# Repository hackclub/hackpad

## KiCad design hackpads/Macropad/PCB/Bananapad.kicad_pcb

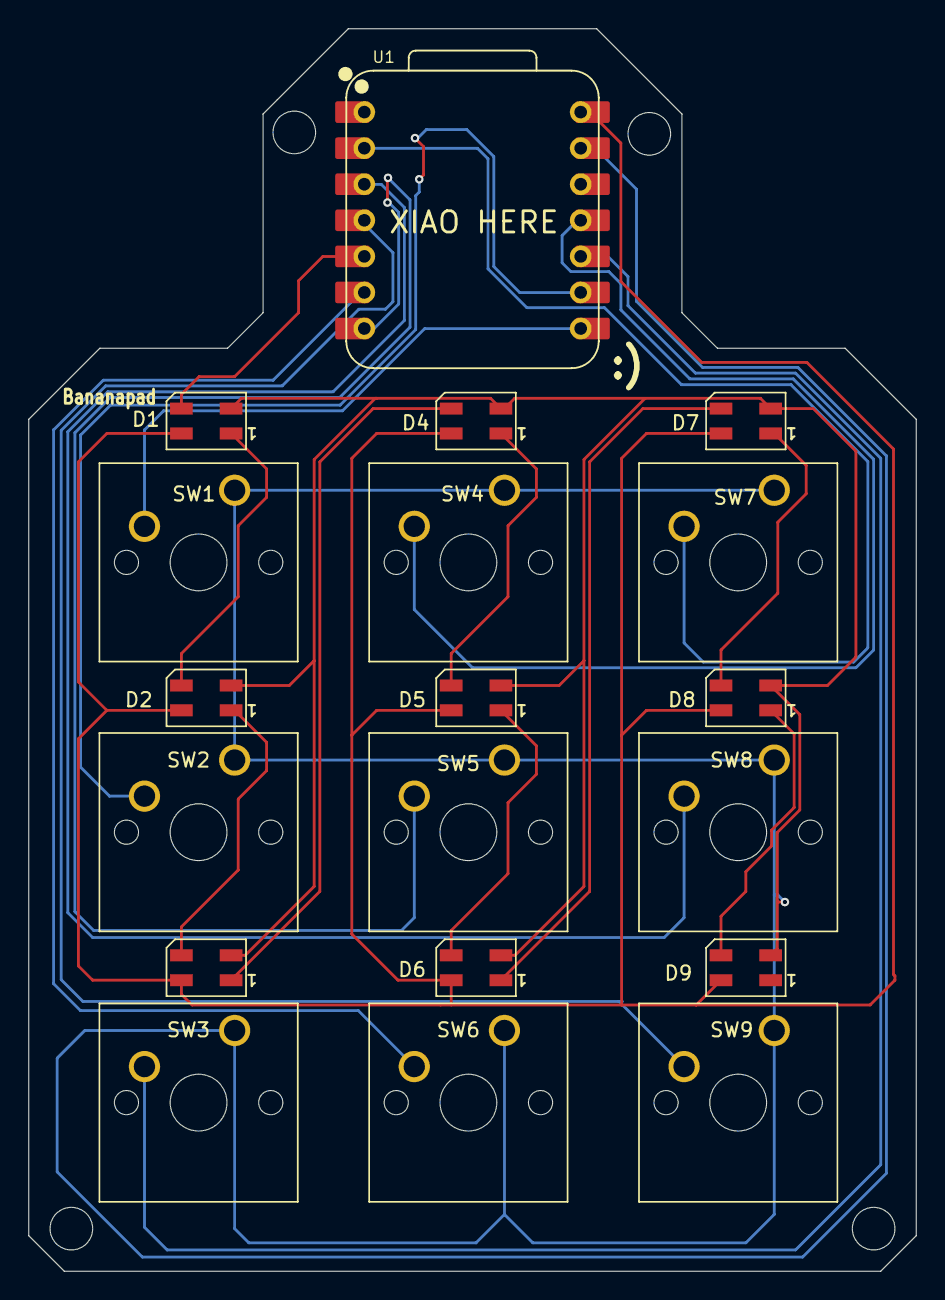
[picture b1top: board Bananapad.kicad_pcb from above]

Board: 2 copper layers, 62.5 x 87.5 mm, 19 parts (0 on the bottom side), 20 nets.

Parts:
D1, D2, D3, D4, D5, D6, D7, D8, D9: SK6812MINI; LED_SK6812MINI_PLCC4_3.5x3.5mm_P1.75mm
SW1, SW2, SW3, SW4, SW5, SW6, SW7, SW8, SW9: SW_Push; SW_Cherry_MX_1.00u_PCB
U1: XIAO-RP2040-DIP

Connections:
+5V: D1.4 (VDD), D2.4 (VDD), D3.4 (VDD), D4.4 (VDD), D5.4 (VDD), D6.4 (VDD), D7.4 (VDD), D8.4 (VDD), D9.4 (VDD), U1.14 (VBUS)
GND: D1.2 (VSS), D2.2 (VSS), D3.2 (VSS), D4.2 (VSS), D5.2 (VSS), D6.2 (VSS), D7.2 (VSS), D8.2 (VSS), D9.2 (VSS), SW1.1, SW2.1, SW3.1, SW4.1, SW5.1, SW6.1, SW7.1, SW8.1, SW9.1, U1.13 (GND)
unnamed: D1.3 (DIN), U1.5 (GPIO6/SDA)
unnamed: D1.1 (DOUT), D2.3 (DIN)
unnamed: D2.1 (DOUT), D3.3 (DIN)
unnamed: D3.1 (DOUT), D4.3 (DIN)
unnamed: D4.1 (DOUT), D5.3 (DIN)
unnamed: D5.1 (DOUT), D6.3 (DIN)
unnamed: D6.1 (DOUT), D7.3 (DIN)
unnamed: D7.1 (DOUT), D8.3 (DIN)
unnamed: D8.1 (DOUT), D9.3 (DIN)
unnamed: SW5.2, U1.7 (GPIO0/TX)
unnamed: SW1.2, U1.8 (GPIO1/RX)
unnamed: SW2.2, U1.9 (GPIO2/SCK)
unnamed: SW4.2, U1.11 (GPIO3/MOSI)
unnamed: SW3.2, U1.10 (GPIO4/MISO)
unnamed: SW6.2, U1.6 (GPIO7/SCL)
unnamed: SW7.2, U1.2 (GPIO27/ADC1/A1)
unnamed: SW8.2, U1.3 (GPIO28/ADC2/A2)
unnamed: SW9.2, U1.4 (GPIO29/ADC3/A3)

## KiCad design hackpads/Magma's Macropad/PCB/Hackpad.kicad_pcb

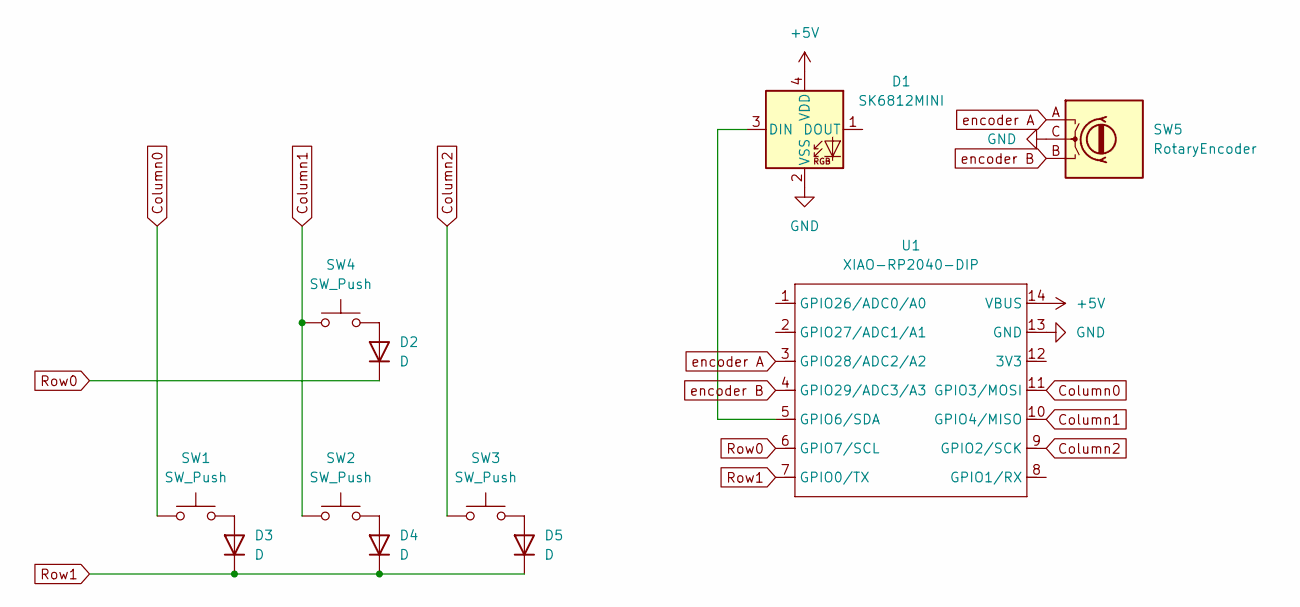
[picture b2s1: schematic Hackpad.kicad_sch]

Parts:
D1: SK6812MINI; LED_SK6812MINI_PLCC4_3.5x3.5mm_P1.75mm
D2, D3, D4, D5: D; D_DO-35_SOD27_P7.62mm_Horizontal
SW1, SW2, SW3, SW4: SW_Push; SW_Cherry_MX_1.00u_PCB
SW5: RotaryEncoder; RotaryEncoder_Alps_EC11E_Vertical_H20mm
U1: XIAO-RP2040-DIP

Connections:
+5V: D1.4 (VDD), U1.14 (VBUS)
Column0: SW1.1, U1.11 (GPIO3/MOSI)
Column1: SW2.1, SW4.1, U1.10 (GPIO4/MISO)
Column2: SW3.1, U1.9 (GPIO2/SCK)
GND: D1.2 (VSS), SW5.C, U1.13 (GND)
unnamed: D1.3 (DIN), U1.5 (GPIO6/SDA)
unnamed: D2.2 (A), SW4.2
unnamed: D3.2 (A), SW1.2
unnamed: D4.2 (A), SW2.2
unnamed: D5.2 (A), SW3.2
Row0: D2.1 (K), U1.6 (GPIO7/SCL)
Row1: D3.1 (K), D4.1 (K), D5.1 (K), U1.7 (GPIO0/TX)
encoder A: SW5.A, U1.3 (GPIO28/ADC2/A2)
encoder B: SW5.B, U1.4 (GPIO29/ADC3/A3)

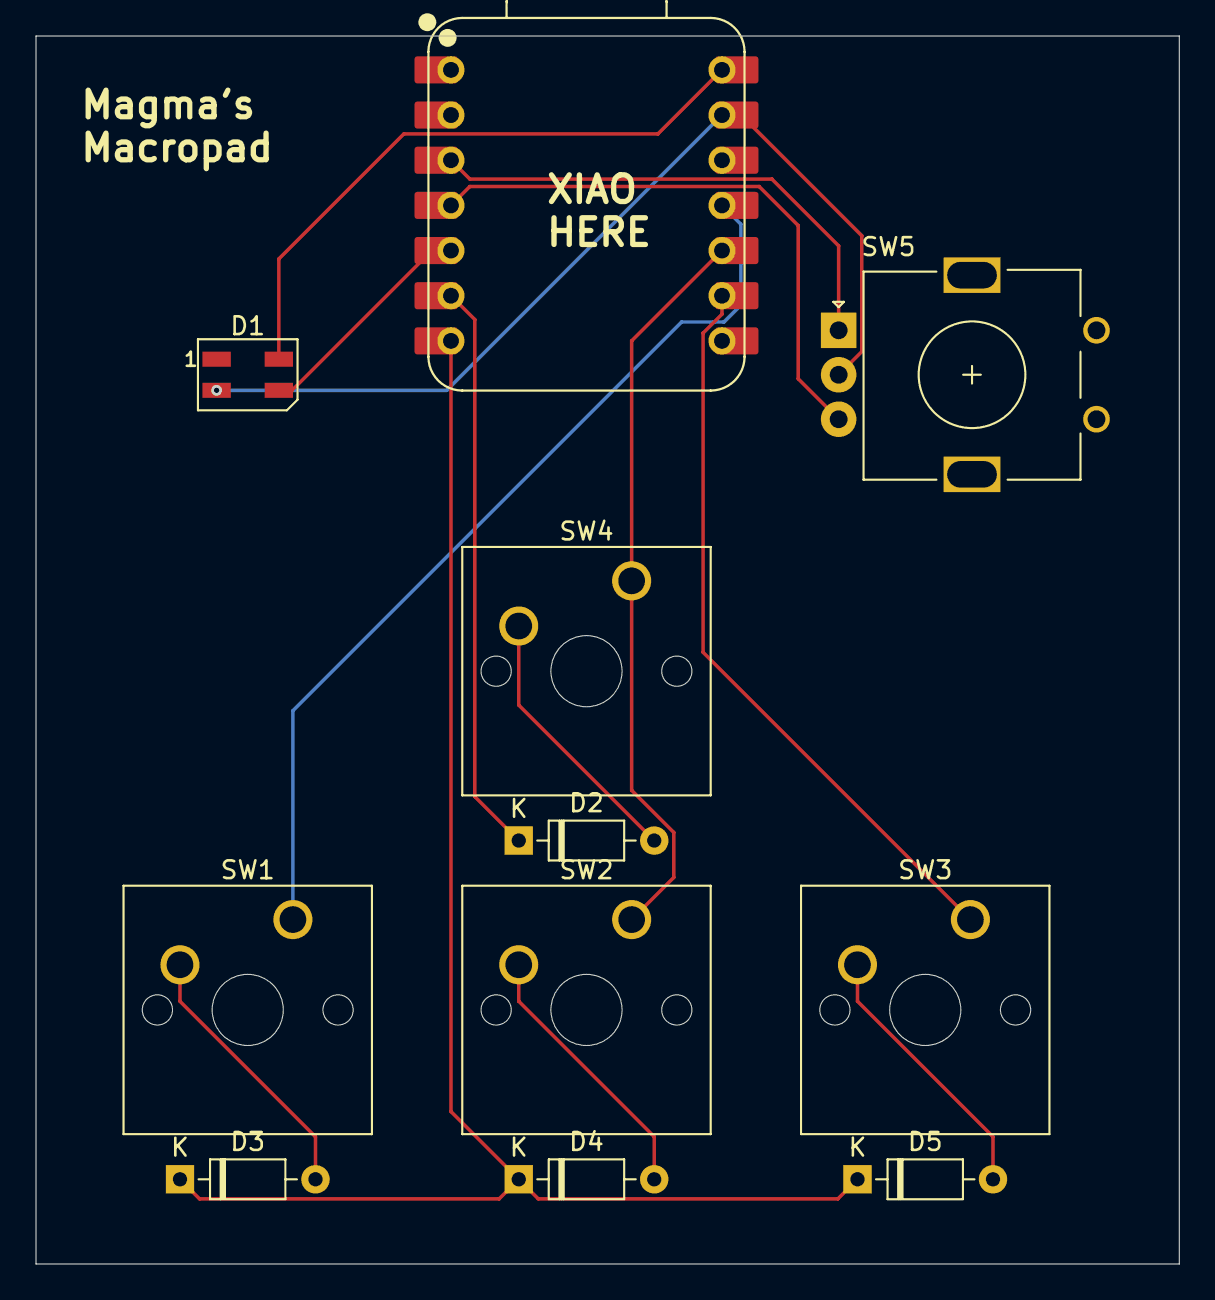
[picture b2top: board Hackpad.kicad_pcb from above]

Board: 2 copper layers, 64.3 x 69.1 mm, 11 parts (0 on the bottom side), 14 nets.

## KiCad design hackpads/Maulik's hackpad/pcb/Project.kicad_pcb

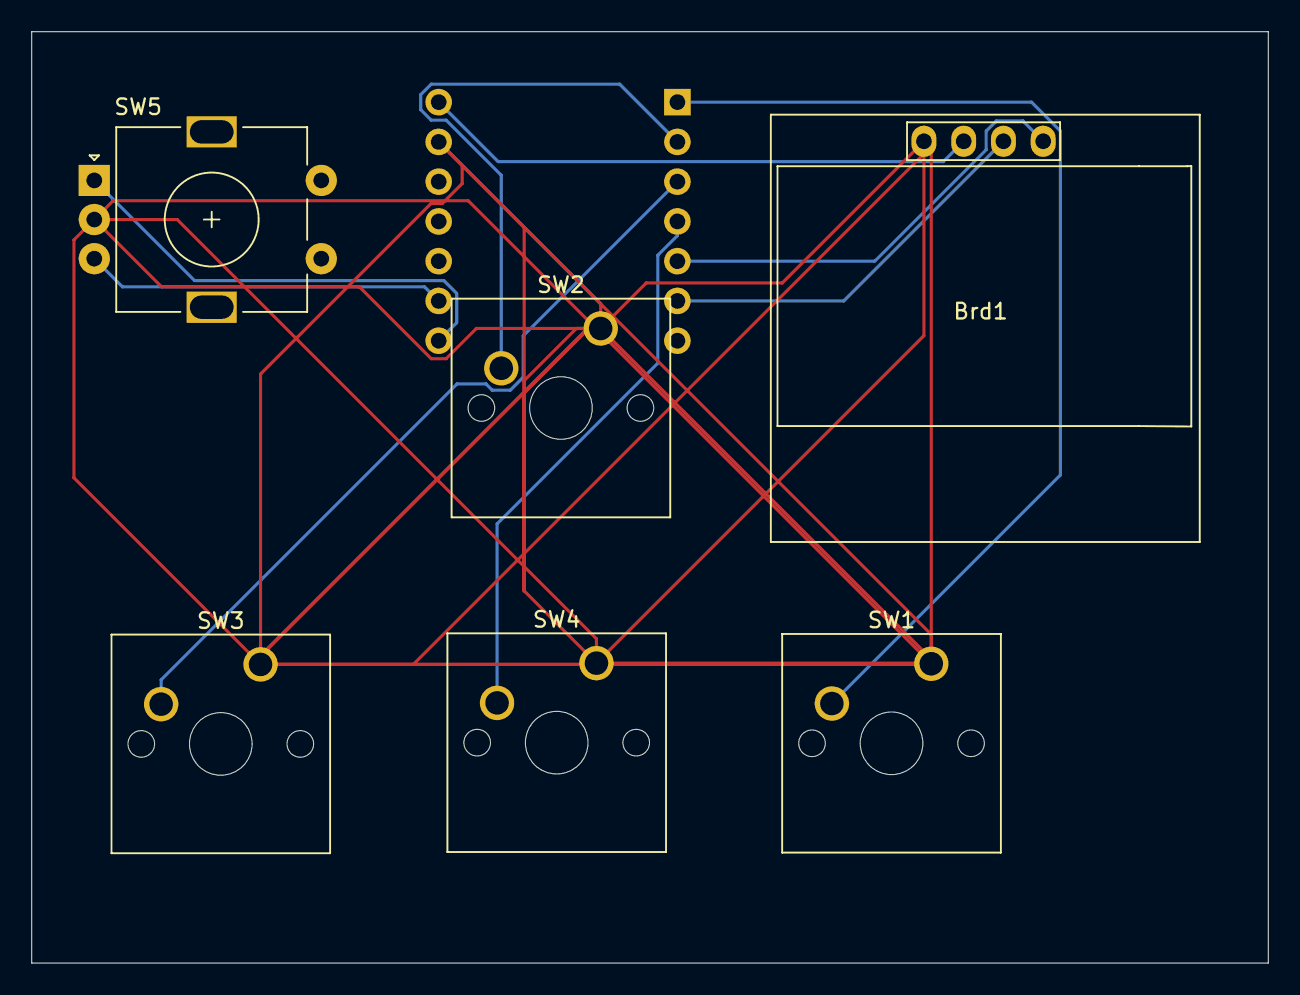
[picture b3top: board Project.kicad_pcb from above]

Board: 2 copper layers, 79.0 x 59.5 mm, 7 parts (1 on the bottom side), 10 nets.

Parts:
Brd1: SSD1306; 128x64OLED
SW1, SW2, SW3, SW4: SW_Push; SW_Cherry_MX_1.00u_PCB
SW5: RotaryEncoder; RotaryEncoder_Alps_EC11E-Switch_Vertical_H20mm
U1: Seeed Studio XIAO SAMD21; XIAO-Generic-Thruhole-14P-2.54-21X17.8MM

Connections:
1: SW1.2, U1.1 (PA02_A0_D0)
2: SW2.2, U1.2 (PA4_A1_D1)
3: SW3.2, U1.3 (PA10_A2_D2)
4: SW4.2, U1.4 (PA11_A3_D3)
A: SW5.A, U1.8 (PB09_A7_D7_RX)
B: SW5.B, U1.9 (PA7_A8_D8_SCK)
GND: Brd1.1 (GND), SW1.1, SW2.1, SW3.1, SW4.1, SW5.C, U1.13 (GND)
SCL: Brd1.3 (SCL), U1.6 (PA9_A5_D5_SCL)
SDA: Brd1.4 (SDA), U1.5 (PA8_A4_D4_SDA)
VCC: Brd1.2 (VCC), U1.14 (5V)

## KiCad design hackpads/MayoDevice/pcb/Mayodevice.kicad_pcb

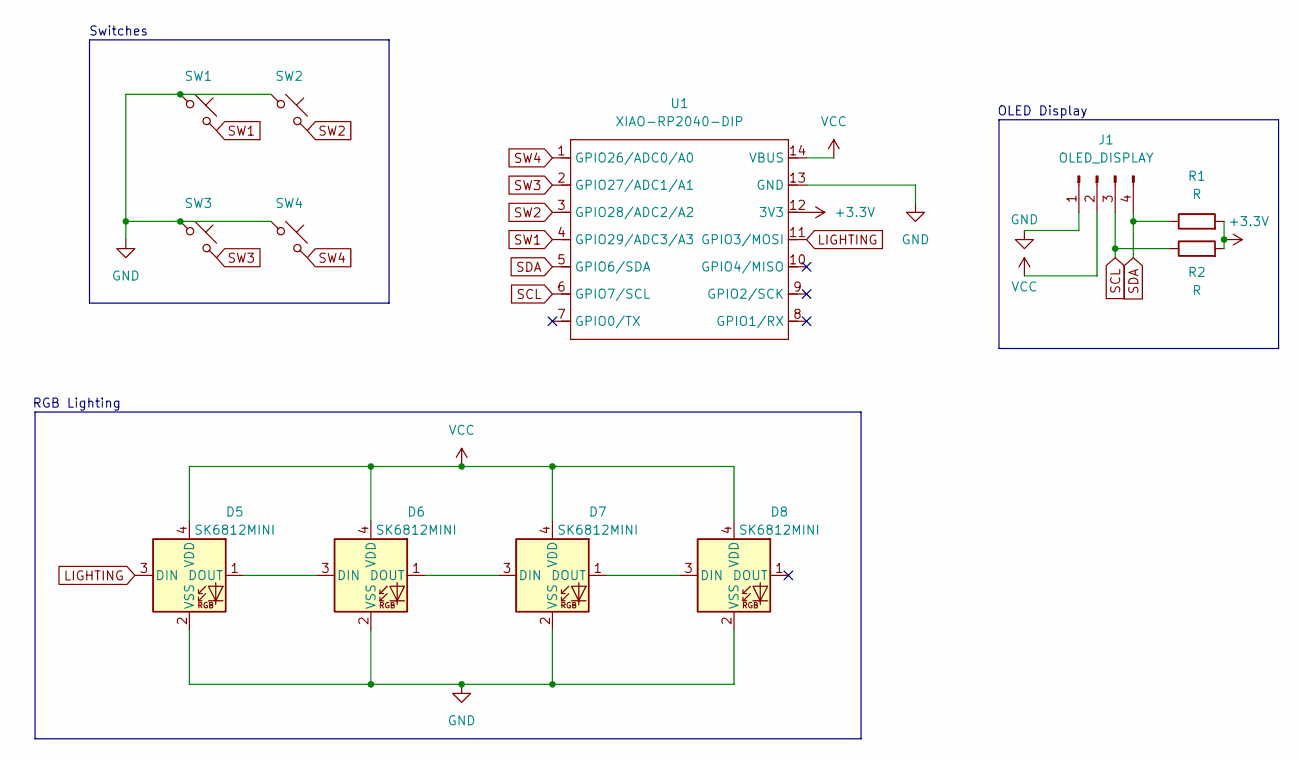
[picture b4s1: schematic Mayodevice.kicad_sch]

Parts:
D5, D6, D7, D8: SK6812MINI; LED_SK6812MINI_PLCC4_3.5x3.5mm_P1.75mm
J1: OLED_DISPLAY; PinHeader_1x04_P2.54mm_Vertical
R1, R2: R; R_Axial_DIN0204_L3.6mm_D1.6mm_P7.62mm_Horizontal
SW1, SW2, SW3, SW4: SW_Push_45deg; Kailh-PG1353-Solderable-1U
U1: XIAO-RP2040-DIP; XIAO-RP2040

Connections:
+3.3V: R1.2, R2.2, U1.12 (3V3)
GND: D5.2 (VSS), D6.2 (VSS), D7.2 (VSS), D8.2 (VSS), J1.1, SW1.1, SW2.1, SW3.1, SW4.1, U1.13 (GND)
LIGHTING: D5.3 (DIN), U1.11 (GPIO3/MOSI)
unnamed: D5.1 (DOUT), D6.3 (DIN)
unnamed: D6.1 (DOUT), D7.3 (DIN)
unnamed: D7.1 (DOUT), D8.3 (DIN)
SCL: J1.3, R2.1, U1.6 (GPIO7/SCL)
SDA: J1.4, R1.1, U1.5 (GPIO6/SDA)
SW1: SW1.2, U1.4 (GPIO29/ADC3/A3)
SW2: SW2.2, U1.3 (GPIO28/ADC2/A2)
SW3: SW3.2, U1.2 (GPIO27/ADC1/A1)
SW4: SW4.2, U1.1 (GPIO26/ADC0/A0)
VCC: D5.4 (VDD), D6.4 (VDD), D7.4 (VDD), D8.4 (VDD), J1.2, U1.14 (VBUS)

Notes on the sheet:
Switches
RGB Lighting
OLED Display

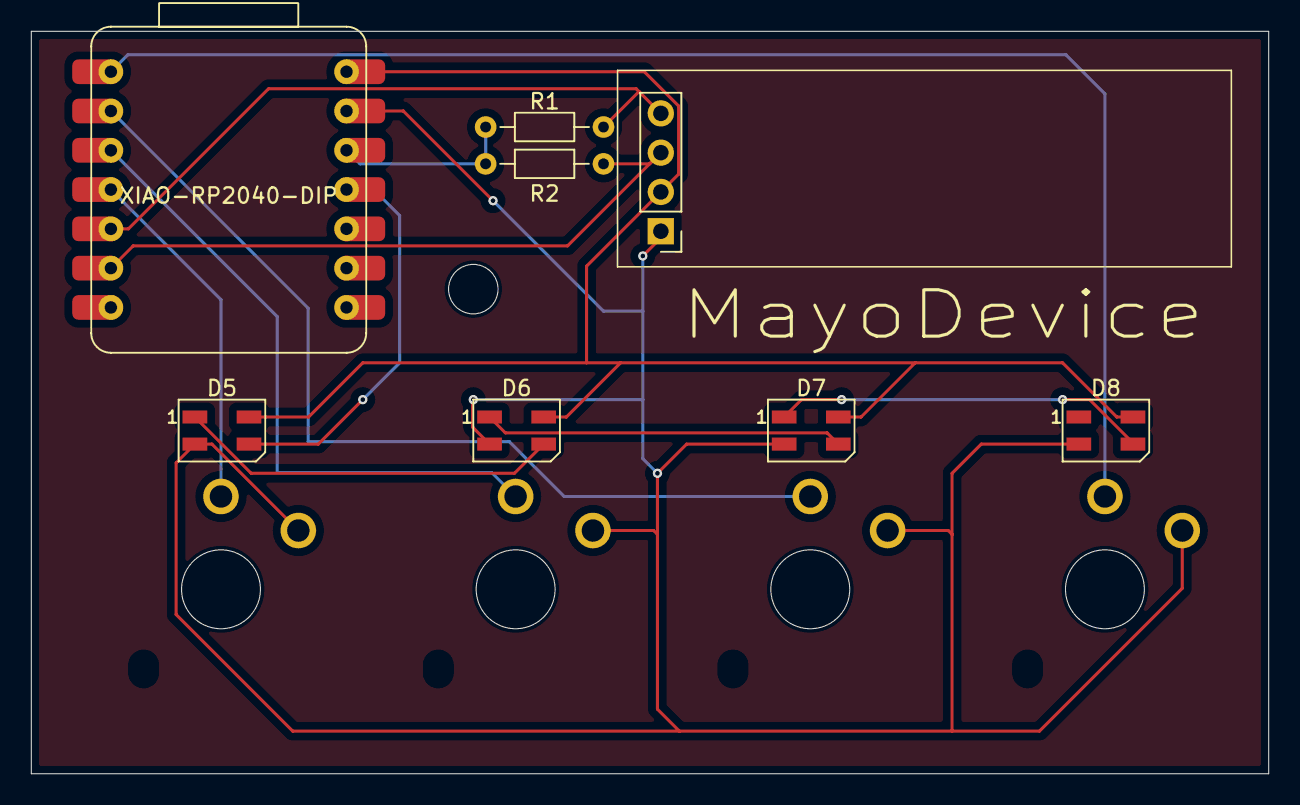
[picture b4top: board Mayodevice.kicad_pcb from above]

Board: 2 copper layers, 80.0 x 48.0 mm, 12 parts (0 on the bottom side), 13 nets.

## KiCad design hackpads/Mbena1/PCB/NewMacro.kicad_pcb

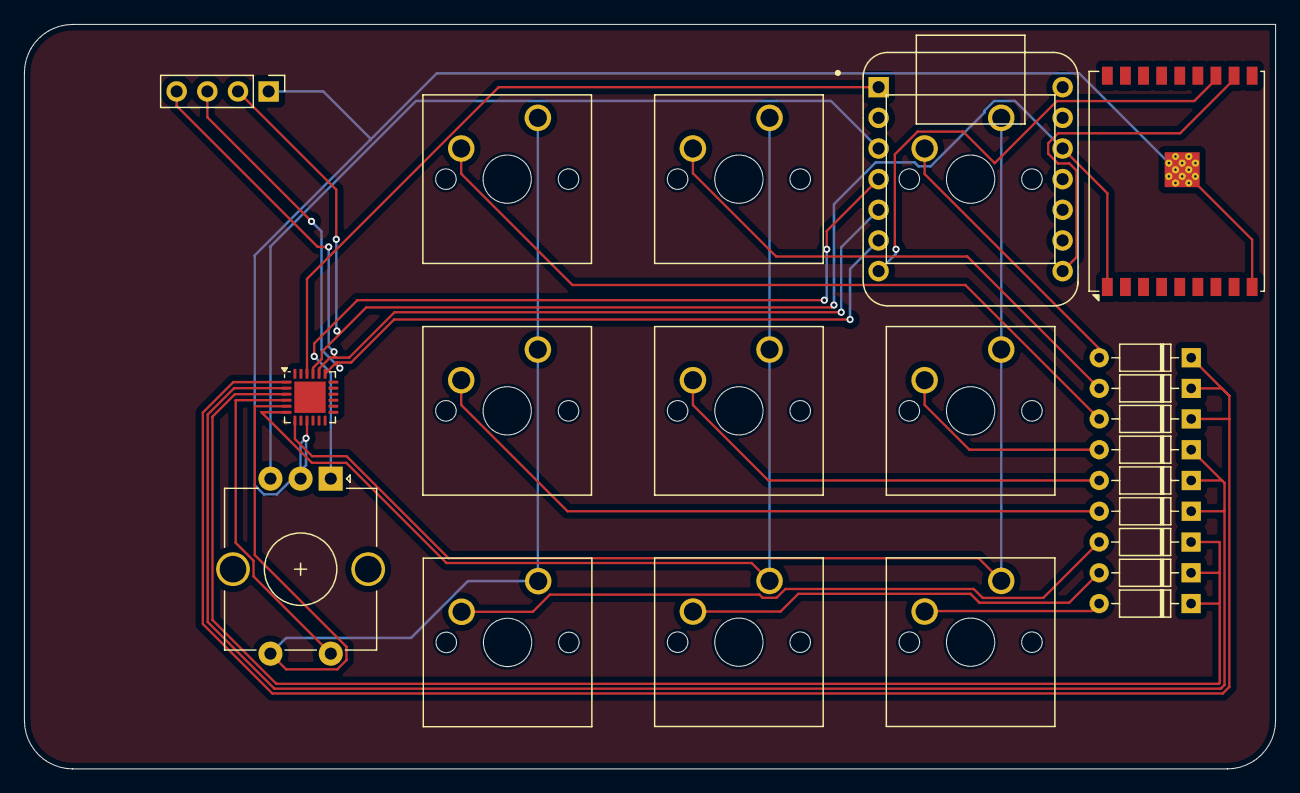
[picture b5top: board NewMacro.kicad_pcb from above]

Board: 2 copper layers, 103.7 x 61.7 mm, 23 parts (0 on the bottom side), 25 nets.

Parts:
D1, D2, D3, D4, D5, D6, D7, D8, D9: D; D_DO-35_SOD27_P7.62mm_Horizontal
J1: Conn_01x04; PinHeader_1x04_P2.54mm_Vertical
SW1, SW2, SW3, SW4, SW5, SW6, SW7, SW8, SW9: SW_Push; SW_Cherry_MX_1.00u_PCB
SW10: RotaryEncoder_Switch; RotaryEncoder_Alps_EC12E-Switch_Vertical_H20mm_CircularMoun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
U2: ESP32-C3-WROOM-02U
U3: STMPE1600; QFN-24-1EP_4x4mm_P0.5mm_EP2.6x2.6mm
U4: Seeed Studio XIAO SAMD21; XIAO-Generic-Thruhole-14P-2.54-21X17.8MM

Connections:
COLUMN 0: SW3.1, SW6.1, SW8.1, SW10.S2, U3.5 (GPIO_4)
COLUMN 1: SW2.1, SW5.1, SW9.1, U3.6 (GPIO_5)
COLUMN 2: SW1.1, SW4.1, SW7.1, U3.7 (GPIO_6)
GND: J1.1, SW10.C, U2.9 (GND), U2.19 (GND), U3.9 (GND)
unnamed: D1.2 (A), SW3.2
unnamed: D2.2 (A), SW8.2
unnamed: D3.2 (A), SW6.2
unnamed: D4.2 (A), SW5.2
unnamed: D5.2 (A), SW9.2
unnamed: D6.2 (A), SW2.2
unnamed: D7.2 (A), SW1.2
unnamed: D8.2 (A), SW7.2
unnamed: D9.2 (A), SW4.2
unnamed: J1.2, U2.1 (3V3), U3.21 (VCC), U4.12 (3V3)
unnamed: J1.3, U3.19 (SCL), U4.6 (PA9_A5_D5_SCL)
unnamed: J1.4, U3.20 (SDA), U4.5 (PA8_A4_D4_SDA)
unnamed: U2.11 (IO20/RXD), U4.8 (PB09_A7_D7_RX)
unnamed: U2.12 (IO21/TXD), U4.7 (PB08_A6_D6_TX)
unnamed: U3.22 (INT), U4.1 (PA02_A0_D0)
unnamed: SW10.B, U4.3 (PA10_A2_D2)
unnamed: SW10.A, U4.4 (PA11_A3_D3)
ROW0: D1.1 (K), D6.1 (K), D7.1 (K), U3.1 (GPIO_0)
ROW1: D2.1 (K), D5.1 (K), D8.1 (K), U3.2 (GPIO_1)
ROW2: D3.1 (K), D4.1 (K), D9.1 (K), U3.3 (GPIO_2)
ROW3: SW10.S1, U3.4 (GPIO_3)

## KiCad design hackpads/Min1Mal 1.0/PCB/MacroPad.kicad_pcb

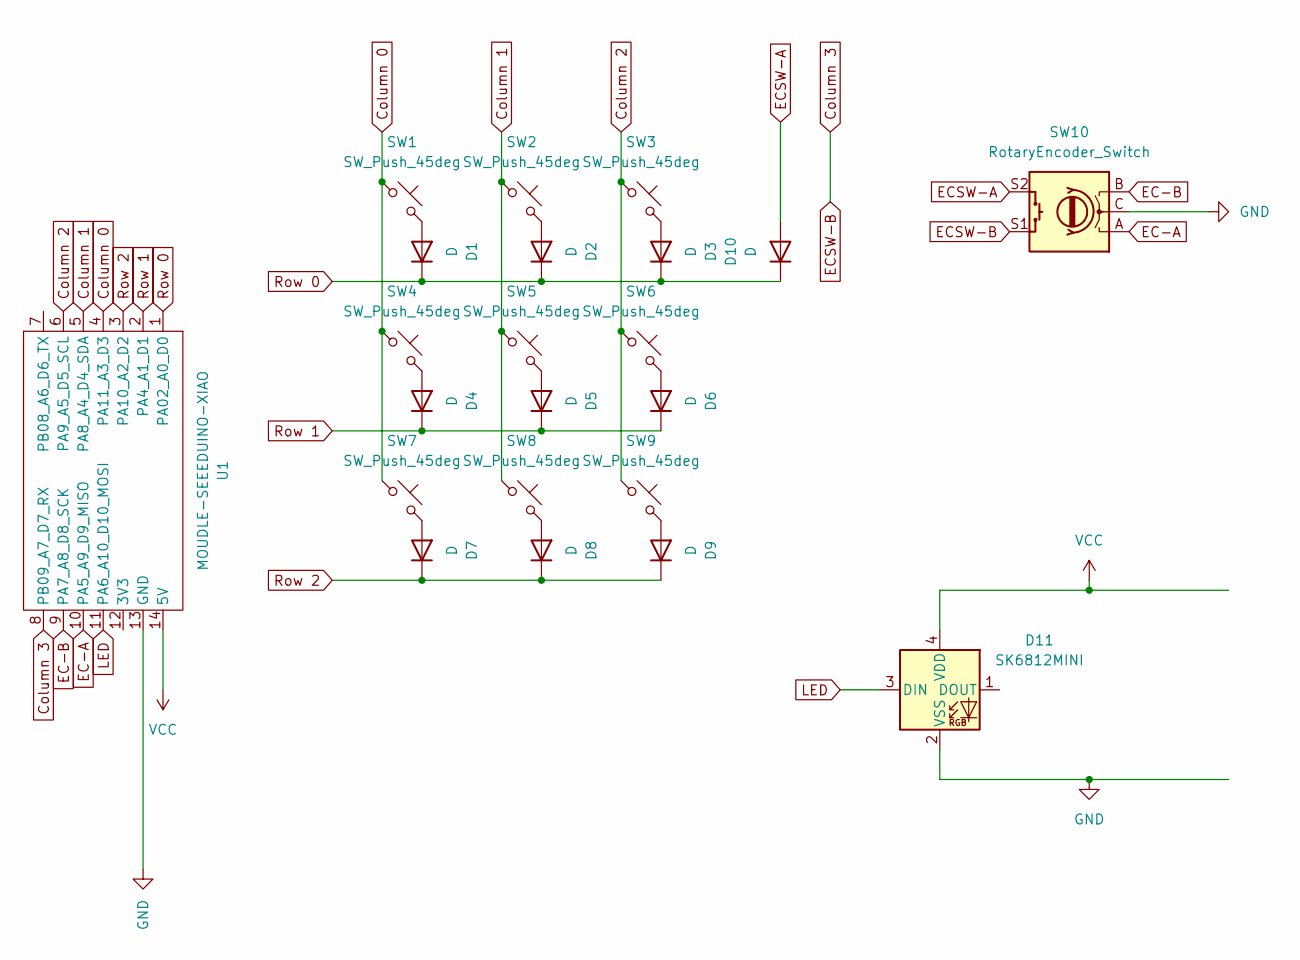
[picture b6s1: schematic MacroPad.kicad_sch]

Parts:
D1, D2, D3, D4, D5, D6, D7, D8, D9, D10: D; D_DO-35_SOD27_P7.62mm_Horizontal
D11: SK6812MINI; LED_SK6812MINI_PLCC4_3.5x3.5mm_P1.75mm
SW1, SW2, SW3, SW4, SW5, SW6, SW7, SW8, SW9: SW_Push_45deg; SW_Cherry_MX_1.00u_PCB
SW10: RotaryEncoder_Switch; RotaryEncoder_Alps_EC11E-Switch_Vertical_H20mm
U1: MOUDLE-SEEEDUINO-XIAO; XIAO-RP2040-DIP

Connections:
Column 0: SW1.1, SW4.1, SW7.1, U1.4 (PA11_A3_D3)
Column 1: SW2.1, SW5.1, SW8.1, U1.5 (PA8_A4_D4_SDA)
Column 2: SW3.1, SW6.1, SW9.1, U1.6 (PA9_A5_D5_SCL)
Column 3: SW10.S1, U1.8 (PB09_A7_D7_RX)
EC-A: SW10.A, U1.10 (PA5_A9_D9_MISO)
EC-B: SW10.B, U1.9 (PA7_A8_D8_SCK)
ECSW-A: D10.2 (A), SW10.S2
GND: D11.2 (VSS), SW10.C, U1.13 (GND)
LED: D11.3 (DIN), U1.11 (PA6_A10_D10_MOSI)
unnamed: D1.2 (A), SW1.2
unnamed: D2.2 (A), SW2.2
unnamed: D3.2 (A), SW3.2
unnamed: D4.2 (A), SW4.2
unnamed: D5.2 (A), SW5.2
unnamed: D6.2 (A), SW6.2
unnamed: D7.2 (A), SW7.2
unnamed: D8.2 (A), SW8.2
unnamed: D9.2 (A), SW9.2
Row 0: D1.1 (K), D2.1 (K), D3.1 (K), D10.1 (K), U1.1 (PA02_A0_D0)
Row 1: D4.1 (K), D5.1 (K), D6.1 (K), U1.2 (PA4_A1_D1)
Row 2: D7.1 (K), D8.1 (K), D9.1 (K), U1.3 (PA10_A2_D2)
VCC: D11.4 (VDD), U1.14 (5V)

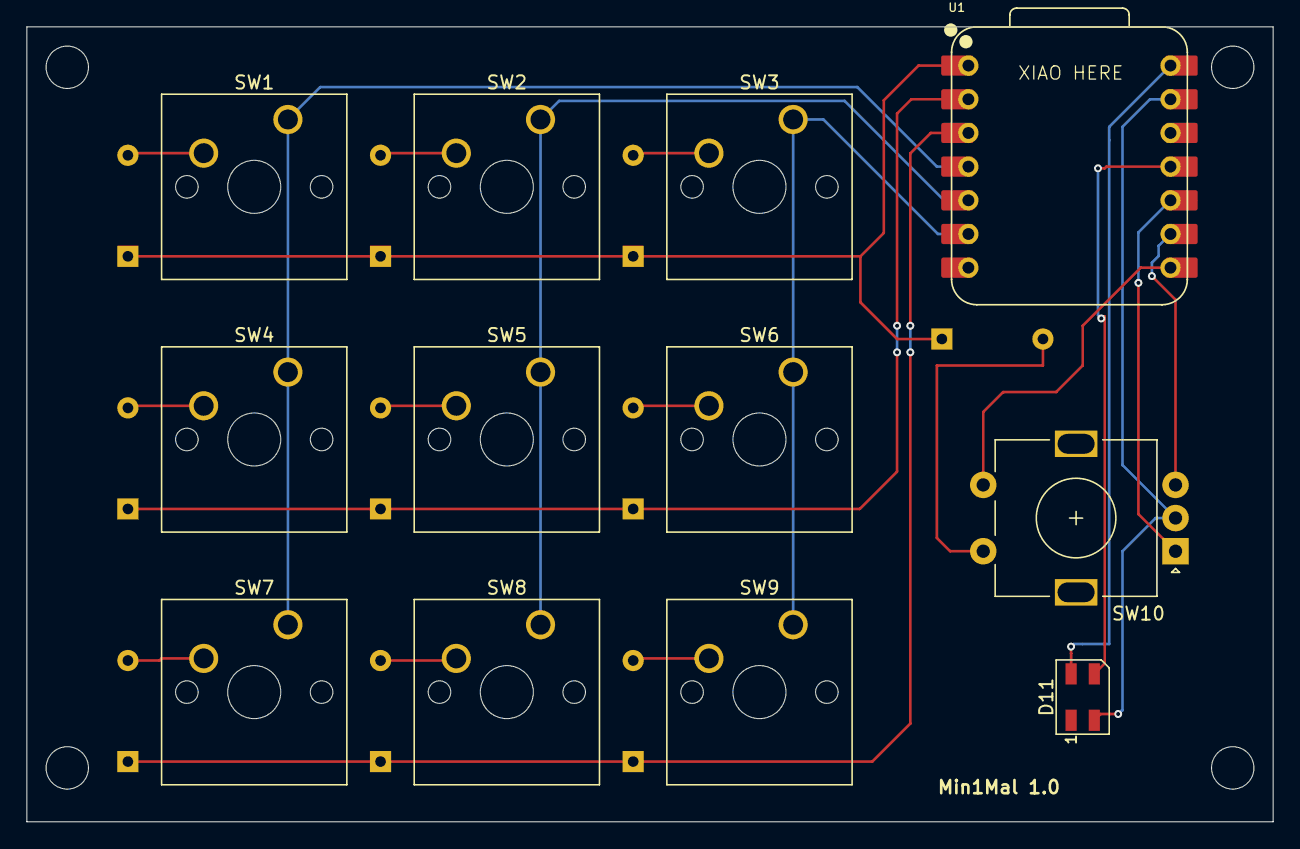
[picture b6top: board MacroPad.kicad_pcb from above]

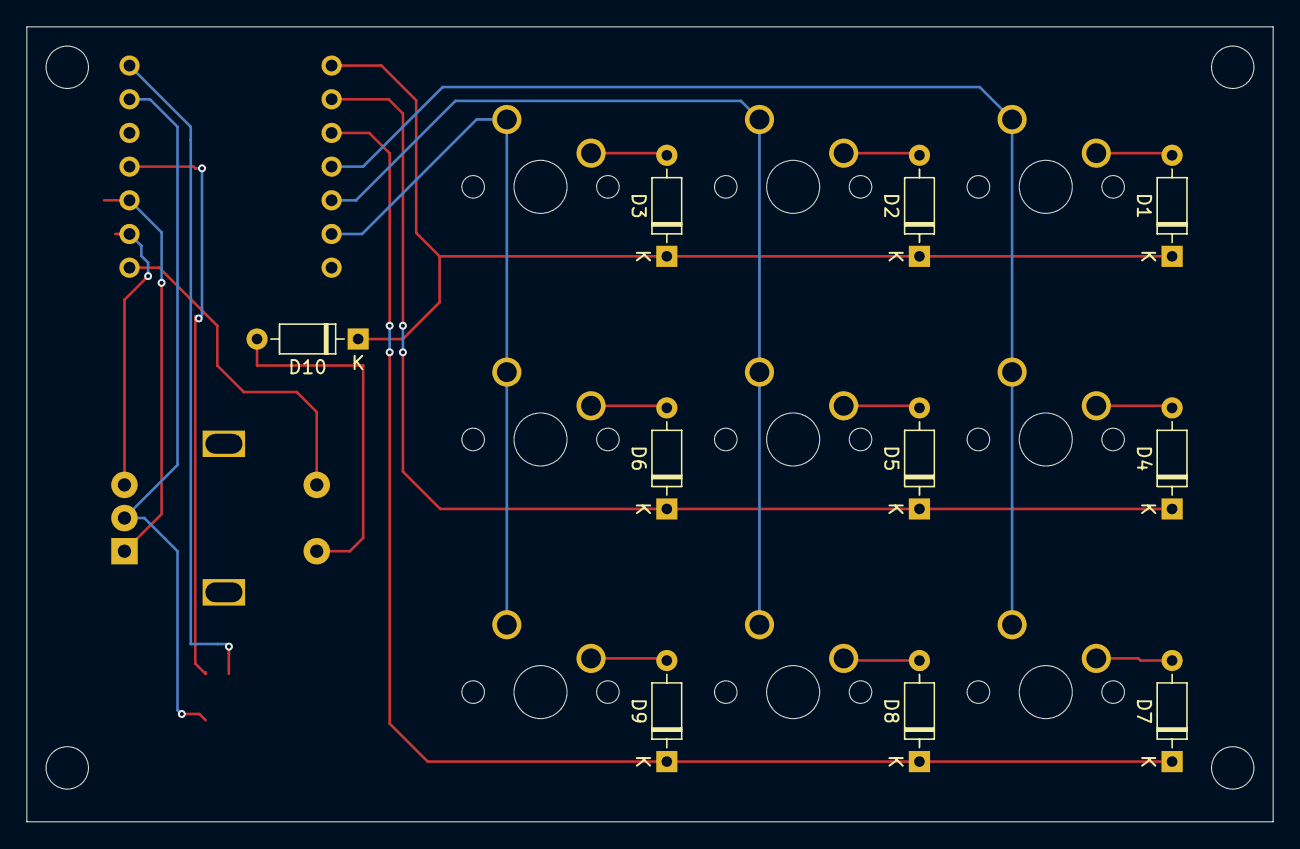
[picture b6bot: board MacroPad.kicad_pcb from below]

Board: 2 copper layers, 94.0 x 59.9 mm, 22 parts (10 on the bottom side), 22 nets.

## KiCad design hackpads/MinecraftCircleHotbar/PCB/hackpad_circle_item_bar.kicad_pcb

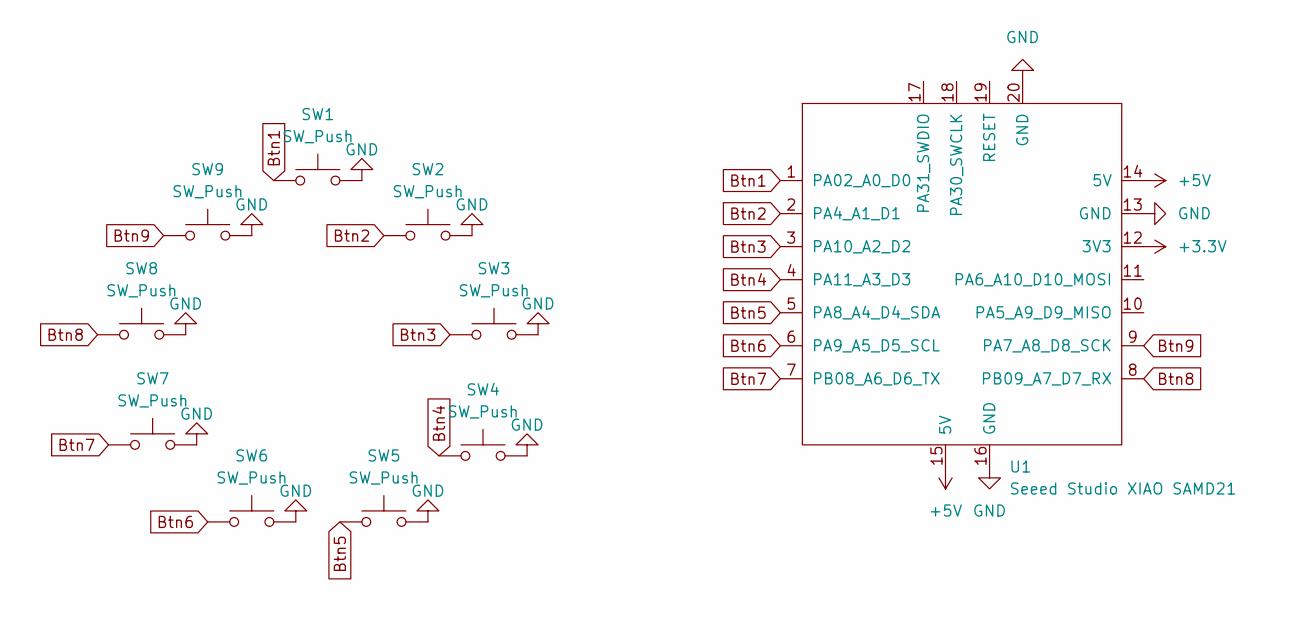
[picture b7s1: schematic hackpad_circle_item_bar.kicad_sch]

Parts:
SW1, SW2, SW3, SW4, SW5, SW6, SW7, SW8, SW9: SW_Push; SW_Cherry_MX_1.00u_PCB
U1: Seeed Studio XIAO SAMD21; XIAO-SAMD21-RP2040-14P-2.54-21X17.8MM (Seeeduino XIAO)

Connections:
+3.3V: U1.12 (3V3)
+5V: U1.14 (5V), U1.15 (5V)
Btn1: SW1.1, U1.1 (PA02_A0_D0)
Btn2: SW2.1, U1.2 (PA4_A1_D1)
Btn3: SW3.1, U1.3 (PA10_A2_D2)
Btn4: SW4.1, U1.4 (PA11_A3_D3)
Btn5: SW5.1, U1.5 (PA8_A4_D4_SDA)
Btn6: SW6.1, U1.6 (PA9_A5_D5_SCL)
Btn7: SW7.1, U1.7 (PB08_A6_D6_TX)
Btn8: SW8.1, U1.8 (PB09_A7_D7_RX)
Btn9: SW9.1, U1.9 (PA7_A8_D8_SCK)
GND: SW1.2, SW2.2, SW3.2, SW4.2, SW5.2, SW6.2, SW7.2, SW8.2, SW9.2, U1.13 (GND), U1.16 (GND), U1.20 (GND)

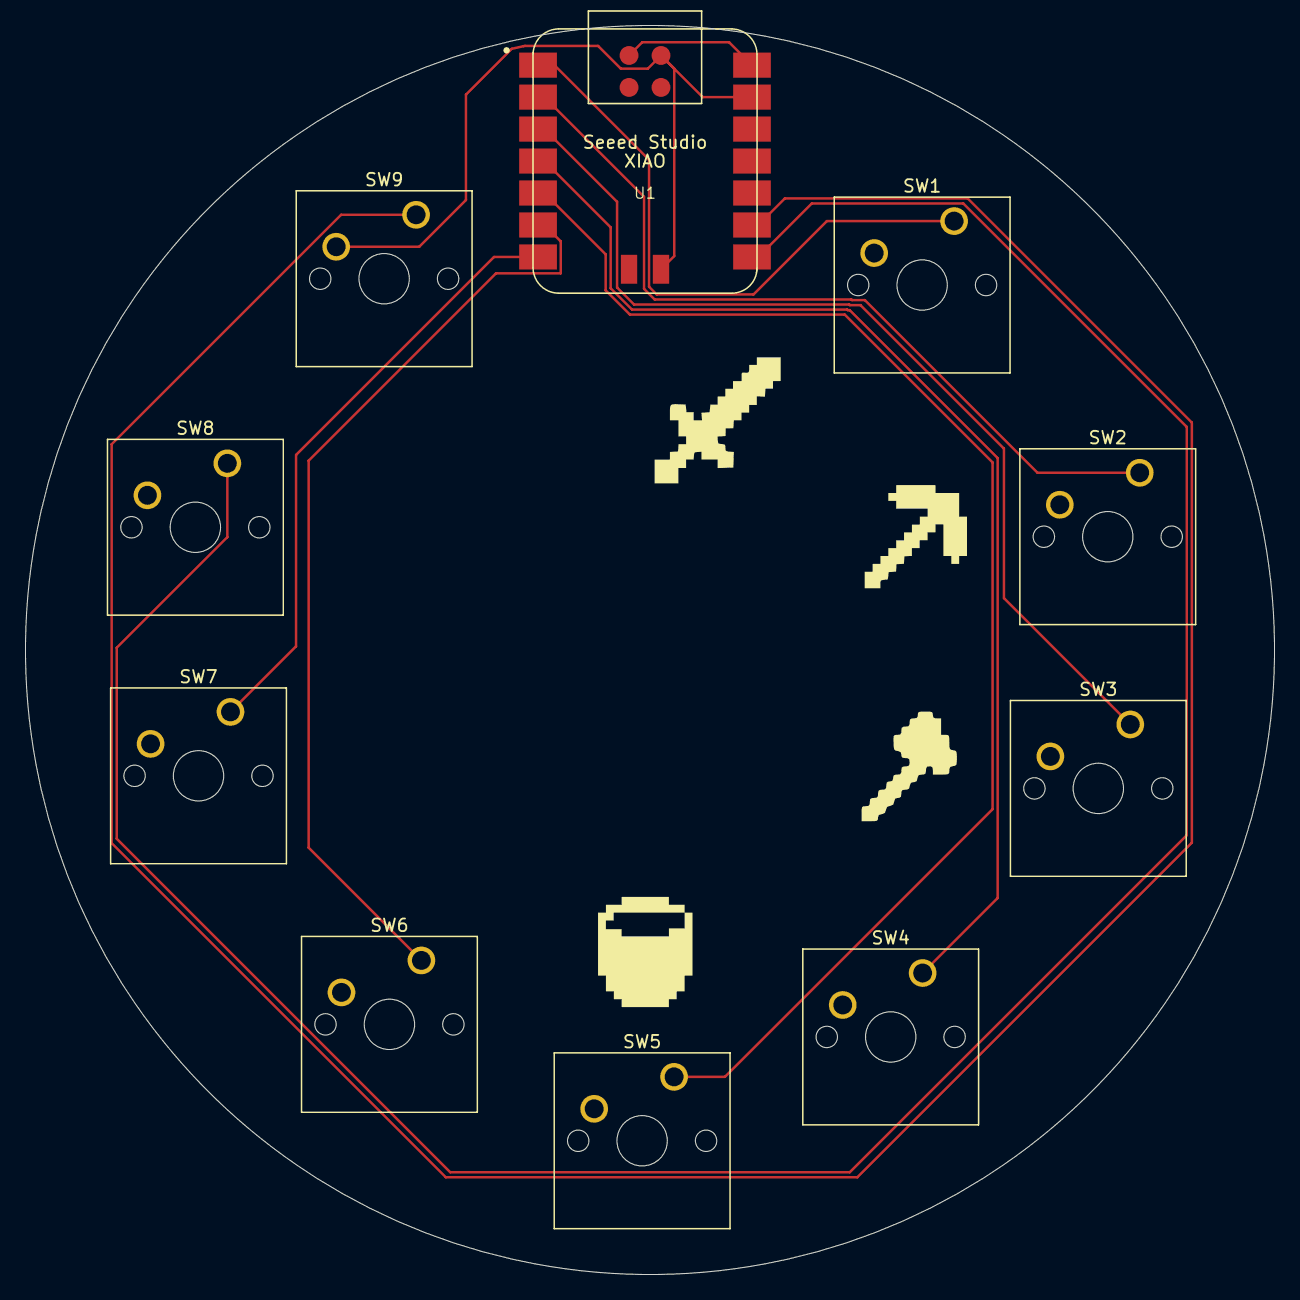
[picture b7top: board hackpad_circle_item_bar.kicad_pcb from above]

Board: 2 copper layers, 99.3 x 99.3 mm, 10 parts (0 on the bottom side), 11 nets.

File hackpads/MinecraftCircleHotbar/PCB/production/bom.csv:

Designator,Footprint,Quantity,Value,LCSC Part #
"SW1, SW2, SW3, SW4, SW5, SW6, SW7, SW8, SW9",SW_Cherry_MX_1.00u_PCB,9,SW_Push,
U1,XIAO-SAMD21-RP2040-14P-2.54-21X17.8MM (Seeeduino XIAO),1,Seeed Studio XIAO SAMD21,
